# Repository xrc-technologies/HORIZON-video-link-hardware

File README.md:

# HORIZON-video-link-hardware
Dev hardware for HORIZON video link

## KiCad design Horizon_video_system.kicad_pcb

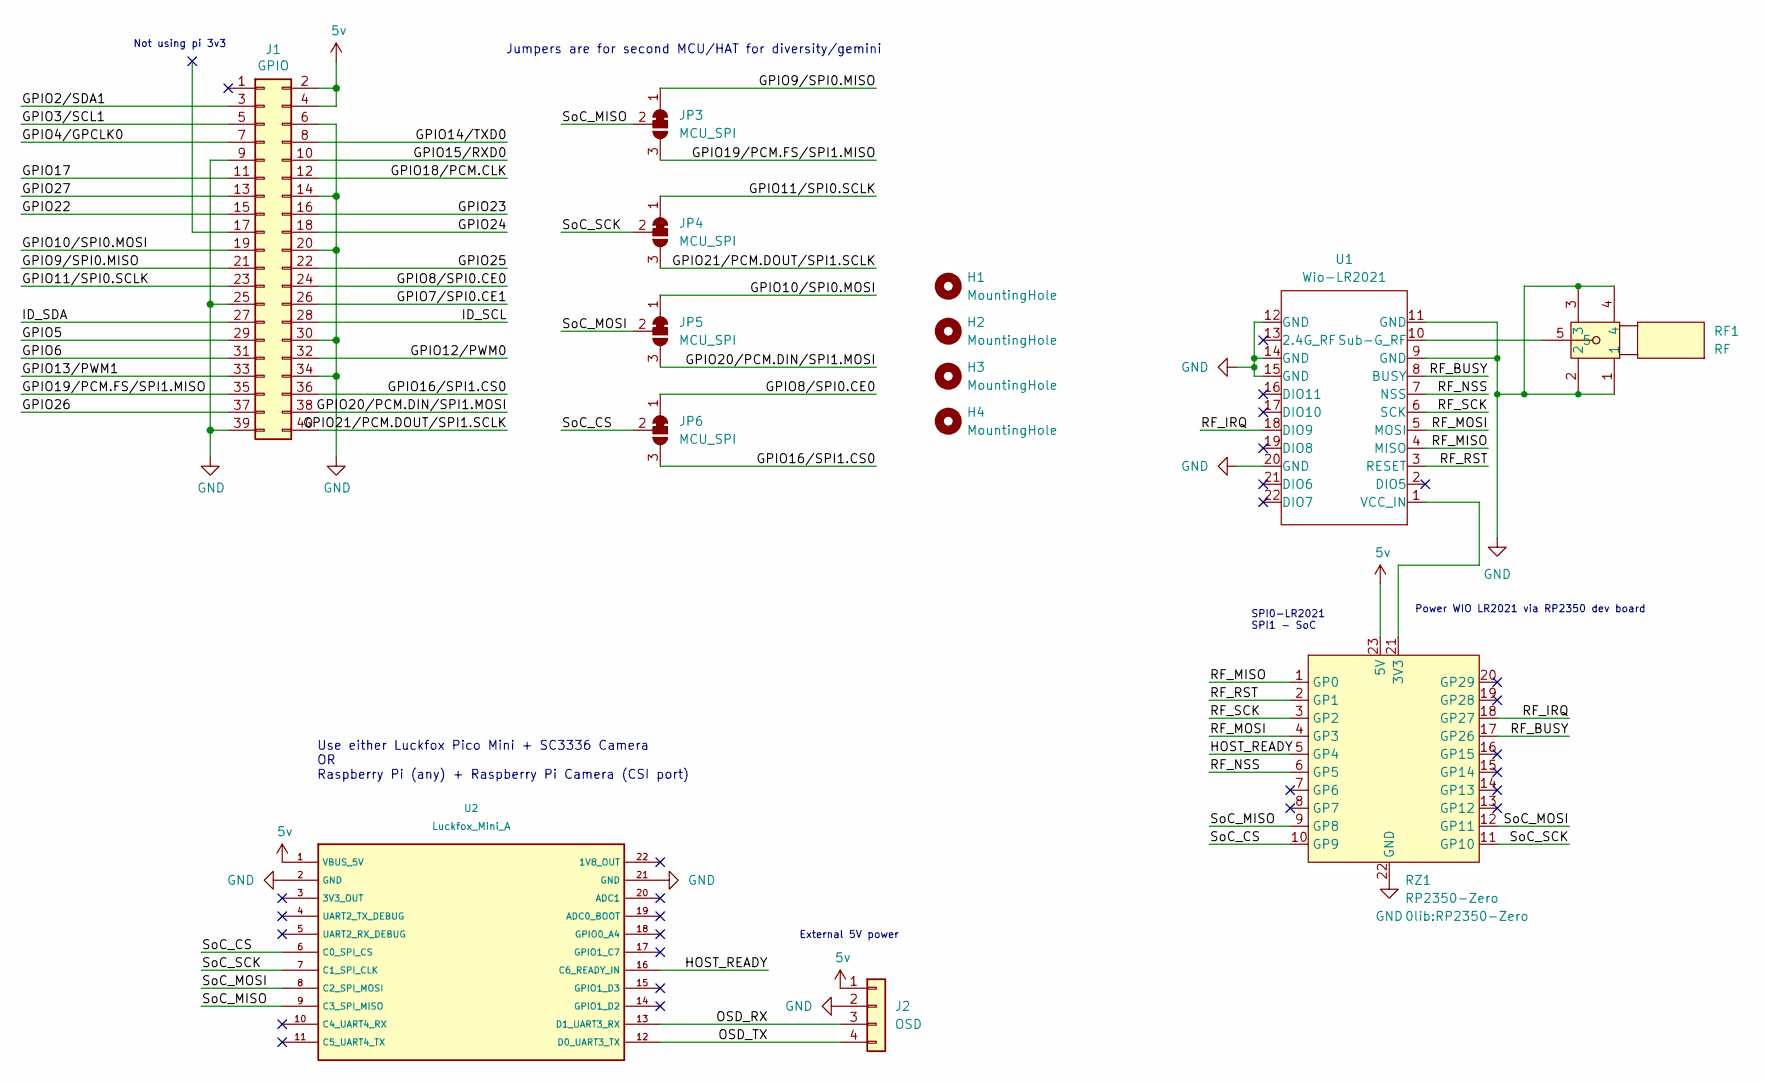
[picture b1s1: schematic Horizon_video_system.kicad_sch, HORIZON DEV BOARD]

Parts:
H1, H2, H3, H4: MountingHole; pi-hole
J1: GPIO; PinSocket_2x20_P2.54mm_Vertical
J2: OSD; PinHeader_1x04_P2.54mm_Vertical
JP3, JP4, JP5, JP6: MCU_SPI; SolderJumper-3_P1.3mm_Bridged2Bar12_RoundedPad1.0x1.5mm
RF1: RF; SMA-SMD_BWSMA-KE-P001; MPN BWSMA-KE-P001; LCSC Part C496550
RZ1: RP2350-Zero
U1: Wio-LR2021; Wio-LR2021_V1
U2: Luckfox_Mini_A; Luckfox_Mini_A_Headers

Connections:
5v: J1.2, J1.4, J2.1, RZ1.23 (5V), U2.1 (VBUS_5V)
/GPIO2/SDA1: J1.3
/GPIO3/SCL1: J1.5
/GPIO4/GPCLK0: J1.7
/GPIO5: J1.29
/GPIO6: J1.31
/GPIO7/SPI0.CE1: J1.26
/GPIO8/SPI0.CE0: J1.24, JP6.1 (A)
/GPIO9/SPI0.MISO: J1.21, JP3.1 (A)
/GPIO10/SPI0.MOSI: J1.19, JP5.1 (A)
/GPIO11/SPI0.SCLK: J1.23, JP4.1 (A)
/GPIO12/PWM0: J1.32
/GPIO13/PWM1: J1.33
/GPIO14/TXD0: J1.8
/GPIO15/RXD0: J1.10
/GPIO16/SPI1.CS0: J1.36, JP6.3 (B)
/GPIO17: J1.11
/GPIO18/PCM.CLK: J1.12
/GPIO19/PCM.FS/SPI1.MISO: J1.35, JP3.3 (B)
/GPIO20/PCM.DIN/SPI1.MOSI: J1.38, JP5.3 (B)
/GPIO21/PCM.DOUT/SPI1.SCLK: J1.40, JP4.3 (B)
/GPIO22: J1.15
/GPIO23: J1.16
/GPIO24: J1.18
/GPIO25: J1.22
/GPIO26: J1.37
/GPIO27: J1.13
/HOST_READY: RZ1.5 (GP4), U2.16 (C6_READY_IN)
/ID_SCL: J1.28
/ID_SDA: J1.27
/OSD_RX: J2.3, U2.13 (D1_UART3_RX)
/OSD_TX: J2.4, U2.12 (D0_UART3_TX)
/RF_BUSY: RZ1.17 (GP26), U1.8 (BUSY)
/RF_IRQ: RZ1.18 (GP27), U1.18 (DIO9)
/RF_MISO: RZ1.1 (GP0), U1.4 (MISO)
/RF_MOSI: RZ1.4 (GP3), U1.5 (MOSI)
/RF_NSS: RZ1.6 (GP5), U1.7 (NSS)
/RF_RST: RZ1.2 (GP1), U1.3 (RESET)
/RF_SCK: RZ1.3 (GP2), U1.6 (SCK)
/SoC_CS: JP6.2 (C), RZ1.10 (GP9), U2.6 (C0_SPI_CS)
/SoC_MISO: JP3.2 (C), RZ1.9 (GP8), U2.9 (C3_SPI_MISO)
/SoC_MOSI: JP5.2 (C), RZ1.12 (GP11), U2.8 (C2_SPI_MOSI)
/SoC_SCK: JP4.2 (C), RZ1.11 (GP10), U2.7 (C1_SPI_CLK)
GND: J1.6, J1.9, J1.14, J1.20, J1.25, J1.30, J1.34, J1.39, J2.2, RF1.1, RF1.2, RF1.3, RF1.4, RZ1.22 (GND), U1.9 (GND), U1.11 (GND), U1.12 (GND), U1.14 (GND), U1.15 (GND), U1.20 (GND), U2.2 (GND), U2.21 (GND)
unnamed: RZ1.21 (3V3), U1.1 (VCC_IN)
unnamed: RF1.5, U1.10 (Sub-G_RF)

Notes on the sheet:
Use either Luckfox Pico Mini + SC3336 Camera OR Raspberry Pi (any) + Raspberry Pi Camera (CSI port)
Power WIO LR2021 via RP2350 dev board
Not using pi 3v3
SPI0-LR2021 SPI1 - SoC
Jumpers are for second MCU/HAT for diversity/gemini
External 5V power

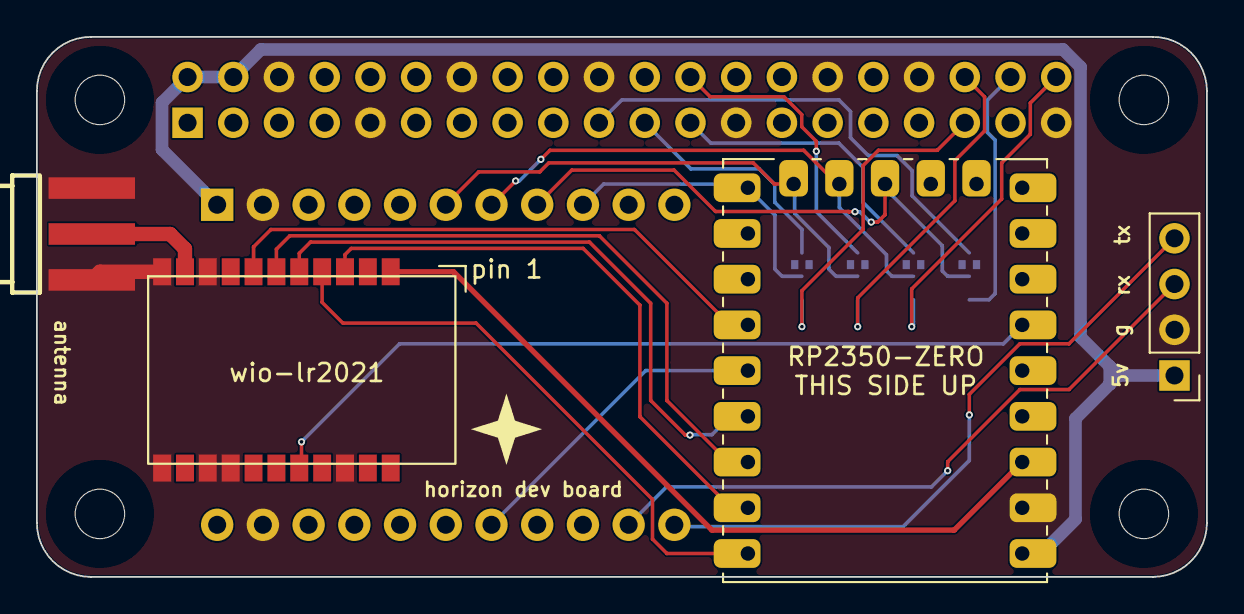
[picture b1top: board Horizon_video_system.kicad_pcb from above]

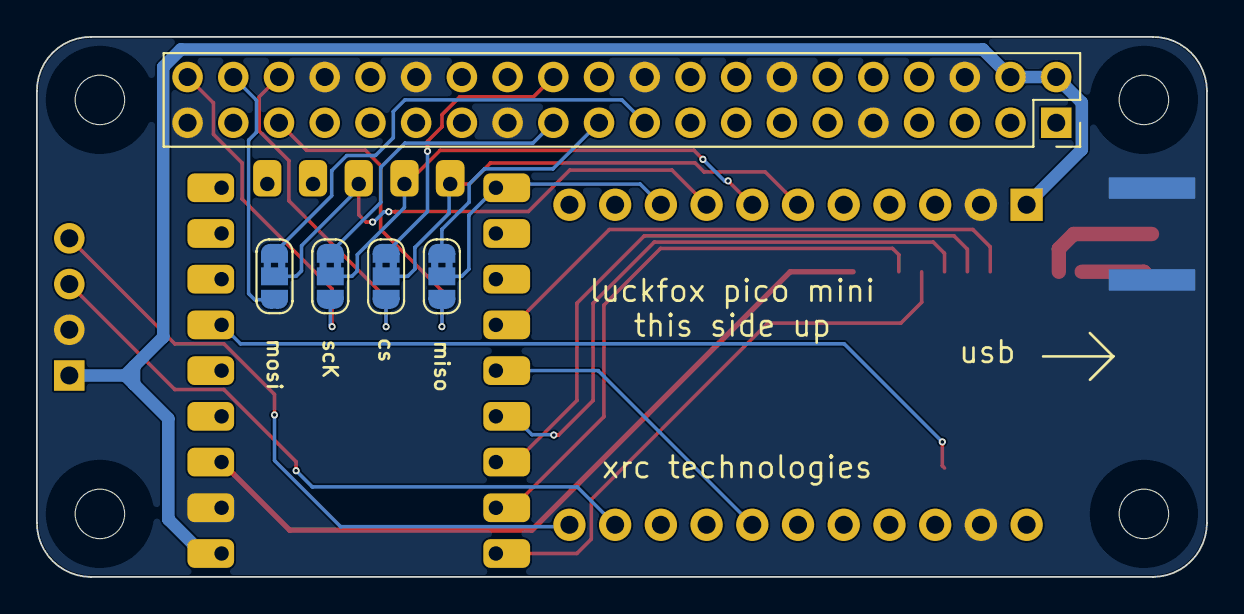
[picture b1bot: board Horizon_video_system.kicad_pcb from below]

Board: 2 copper layers, 65.0 x 30.0 mm, 14 parts (6 on the bottom side), 26 nets.

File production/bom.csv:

Designator,Footprint,Quantity,Value,LCSC Part #
J1,PinSocket_2x20_P2.54mm_Vertical,1,GPIO,
J2,PinHeader_1x04_P2.54mm_Vertical,1,OSD,
RF1,SMA-SMD_BWSMA-KE-P001,1,RF,C496550
RZ1,RP2350-Zero,1,RP2350-Zero,
U1,Wio-LR2021_V1,1,Wio-LR2021, 
U2,Luckfox_Mini_A_Headers,1,Luckfox_Mini_A,Luckfox Pico Mini A
